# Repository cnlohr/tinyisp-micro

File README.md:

tinyisp-micro
=============

My USBTinyISP (with an ATTiny44)

Available from OSH Park here:
	https://oshpark.com/shared_projects/ijclv4pr

BOM Is pretty cheap.  Check the kicad folder for more info.  The file is called
tinyispmicro.lst.

Firmware is slightly modified from the regular USBTinyISP.

I recommend flashing using the .hex file provided in:
	firmware/spi/main.hex.

Flash the AVR by conneting the "PGM" pin and another programmer.

Don't forget fuses!!!

Once flashed, disconnect the "pgm" option and connect the "REG" option.

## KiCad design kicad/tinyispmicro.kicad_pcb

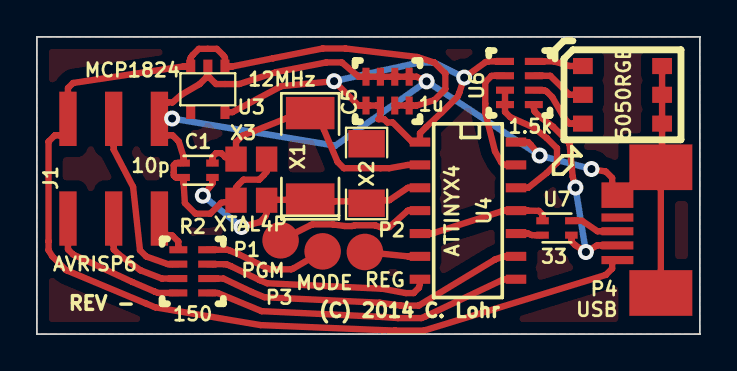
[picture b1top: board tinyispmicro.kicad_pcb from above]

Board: 2 copper layers, 36.8 x 16.5 mm, 16 parts (0 on the bottom side), 24 nets.

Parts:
C1: 10p; NETWORK0606
C5: 1u; NETWORK1206
D1: 5050RGB
J1: AVRISP6; RIBBON6SMT
P1: PGM; .1SMTPIN
P2: REG; .1SMTPIN
P3: MODE; .1SMTPIN
P4: USB; USB-MiniB
R2: 150; NETWORK1206
U3: MCP1824; SOT23-5
U4: ATTINYX4; SO14E
U6: 1.5k; NETWORK1206
U7: 33; NETWORK0606
X1: 12MHz; SM2010
X2: 12MHz; SM1206
X3: XTAL4P

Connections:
+3.3V: C5.1, C5.2, U3.5, U4.1, U6.1
+5V: C5.3, C5.4, J1.2, P4.1, U3.1, U3.3
GND: C1.1, C1.3, C5.5, C5.6, C5.7, C5.8, D1.4, D1.5, D1.6, J1.6, P4.5, P4.6, P4.7, U3.2, U4.14, X3.3, X3.4
unnamed: P3.1, R2.4
unnamed: J1.5, R2.5
unnamed: R2.3, U4.7
unnamed: J1.4, R2.6
unnamed: P1.1, U4.4
unnamed: D1.3, U6.6
unnamed: P2.1, U4.6
unnamed: D1.2, U6.7
unnamed: U4.13, U6.2
unnamed: D1.1, U6.8
unnamed: C1.2, U4.2, X1.2, X3.2
unnamed: C1.4, U4.3, X1.1, X2.1, X3.1
unnamed: P4.2, U6.5, U7.4
unnamed: U4.12, U6.3, U6.4
unnamed: P4.3, U7.2
unnamed: J1.1, R2.8
unnamed: J1.3, R2.7
unnamed: R2.1, U4.8
unnamed: R2.2, U4.9
unnamed: U4.5, U4.11, U7.1
unnamed: U4.10, U7.3

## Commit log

2014-11-14 just dump the project over to github
2014-12-18 fix part number for USB connector
2014-12-18 fix readme
2014-12-18 fix price
2017-07-12 add new rev and update design

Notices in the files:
kicad/tinyispmicro.kicad_pcb:
(C) 2014 C. Lohr
